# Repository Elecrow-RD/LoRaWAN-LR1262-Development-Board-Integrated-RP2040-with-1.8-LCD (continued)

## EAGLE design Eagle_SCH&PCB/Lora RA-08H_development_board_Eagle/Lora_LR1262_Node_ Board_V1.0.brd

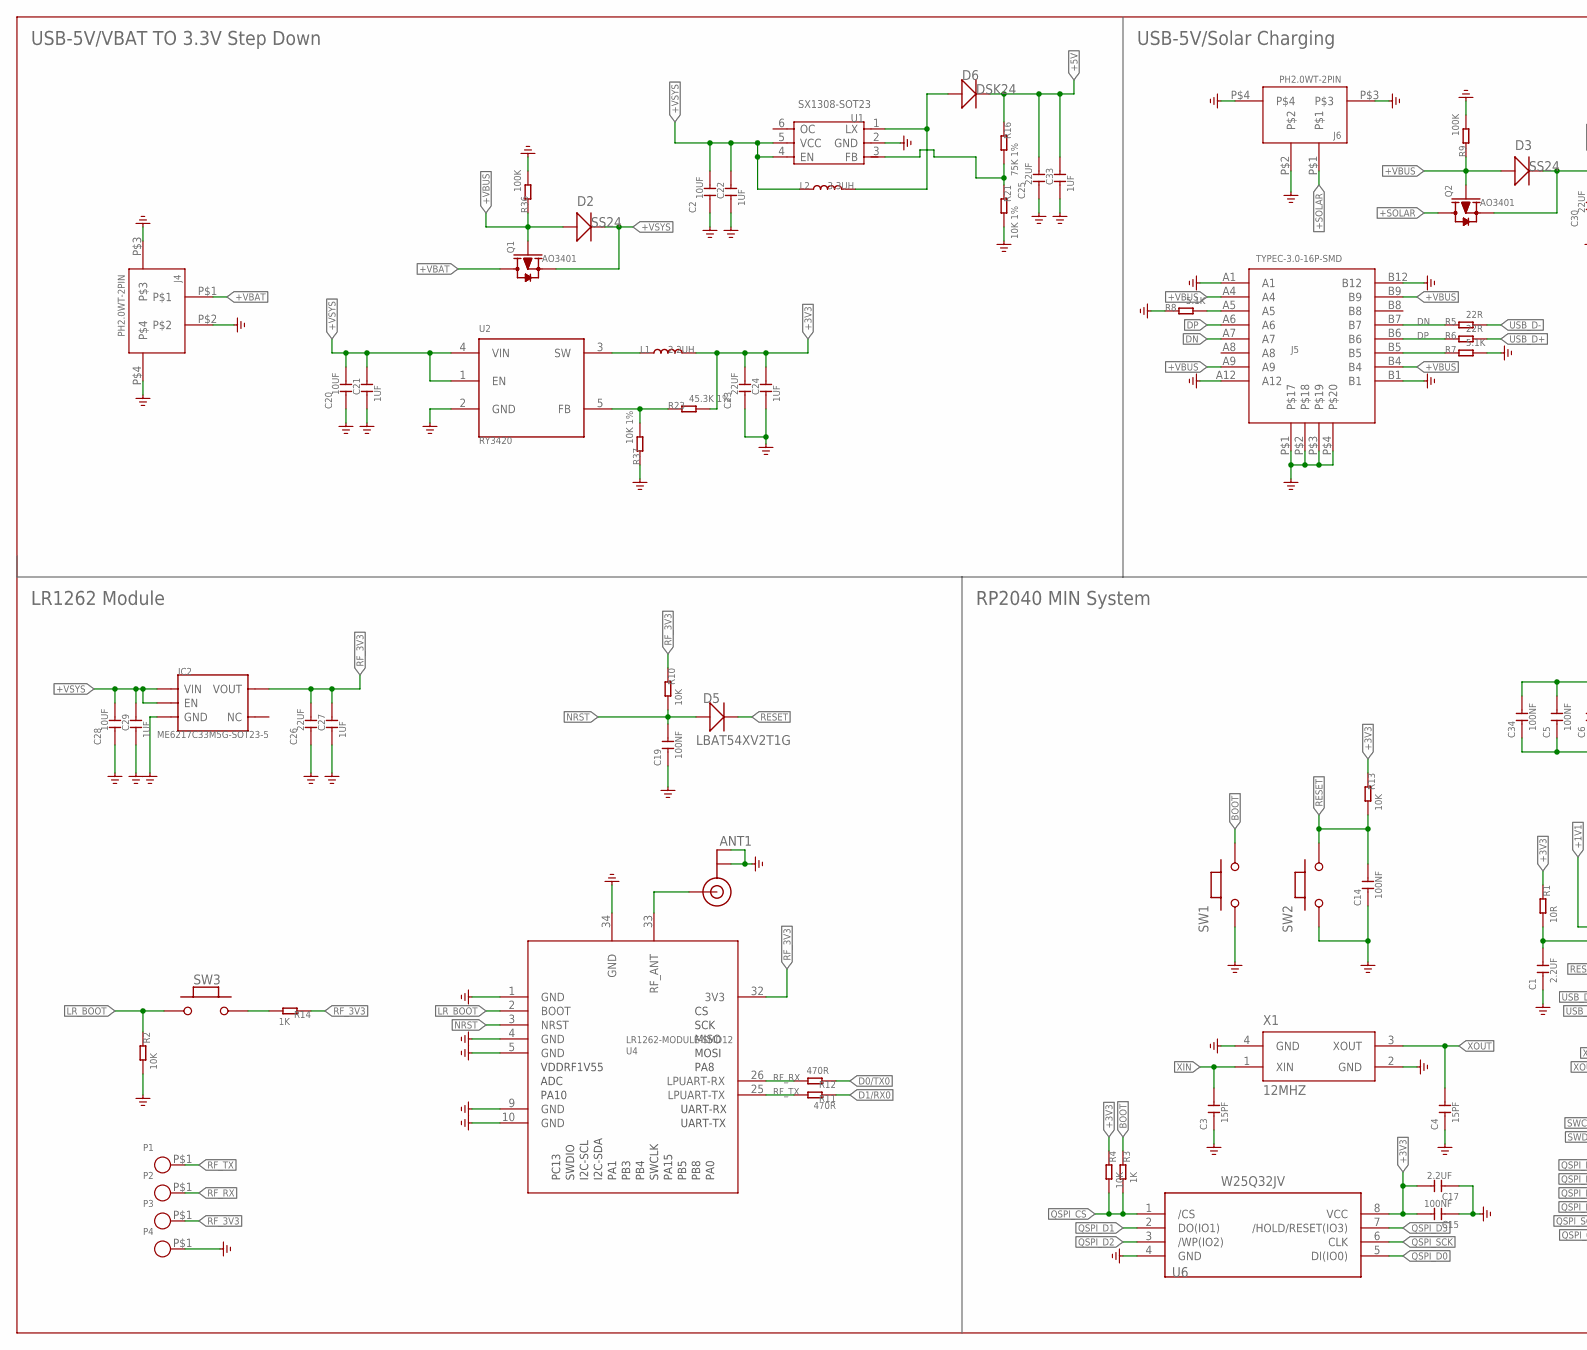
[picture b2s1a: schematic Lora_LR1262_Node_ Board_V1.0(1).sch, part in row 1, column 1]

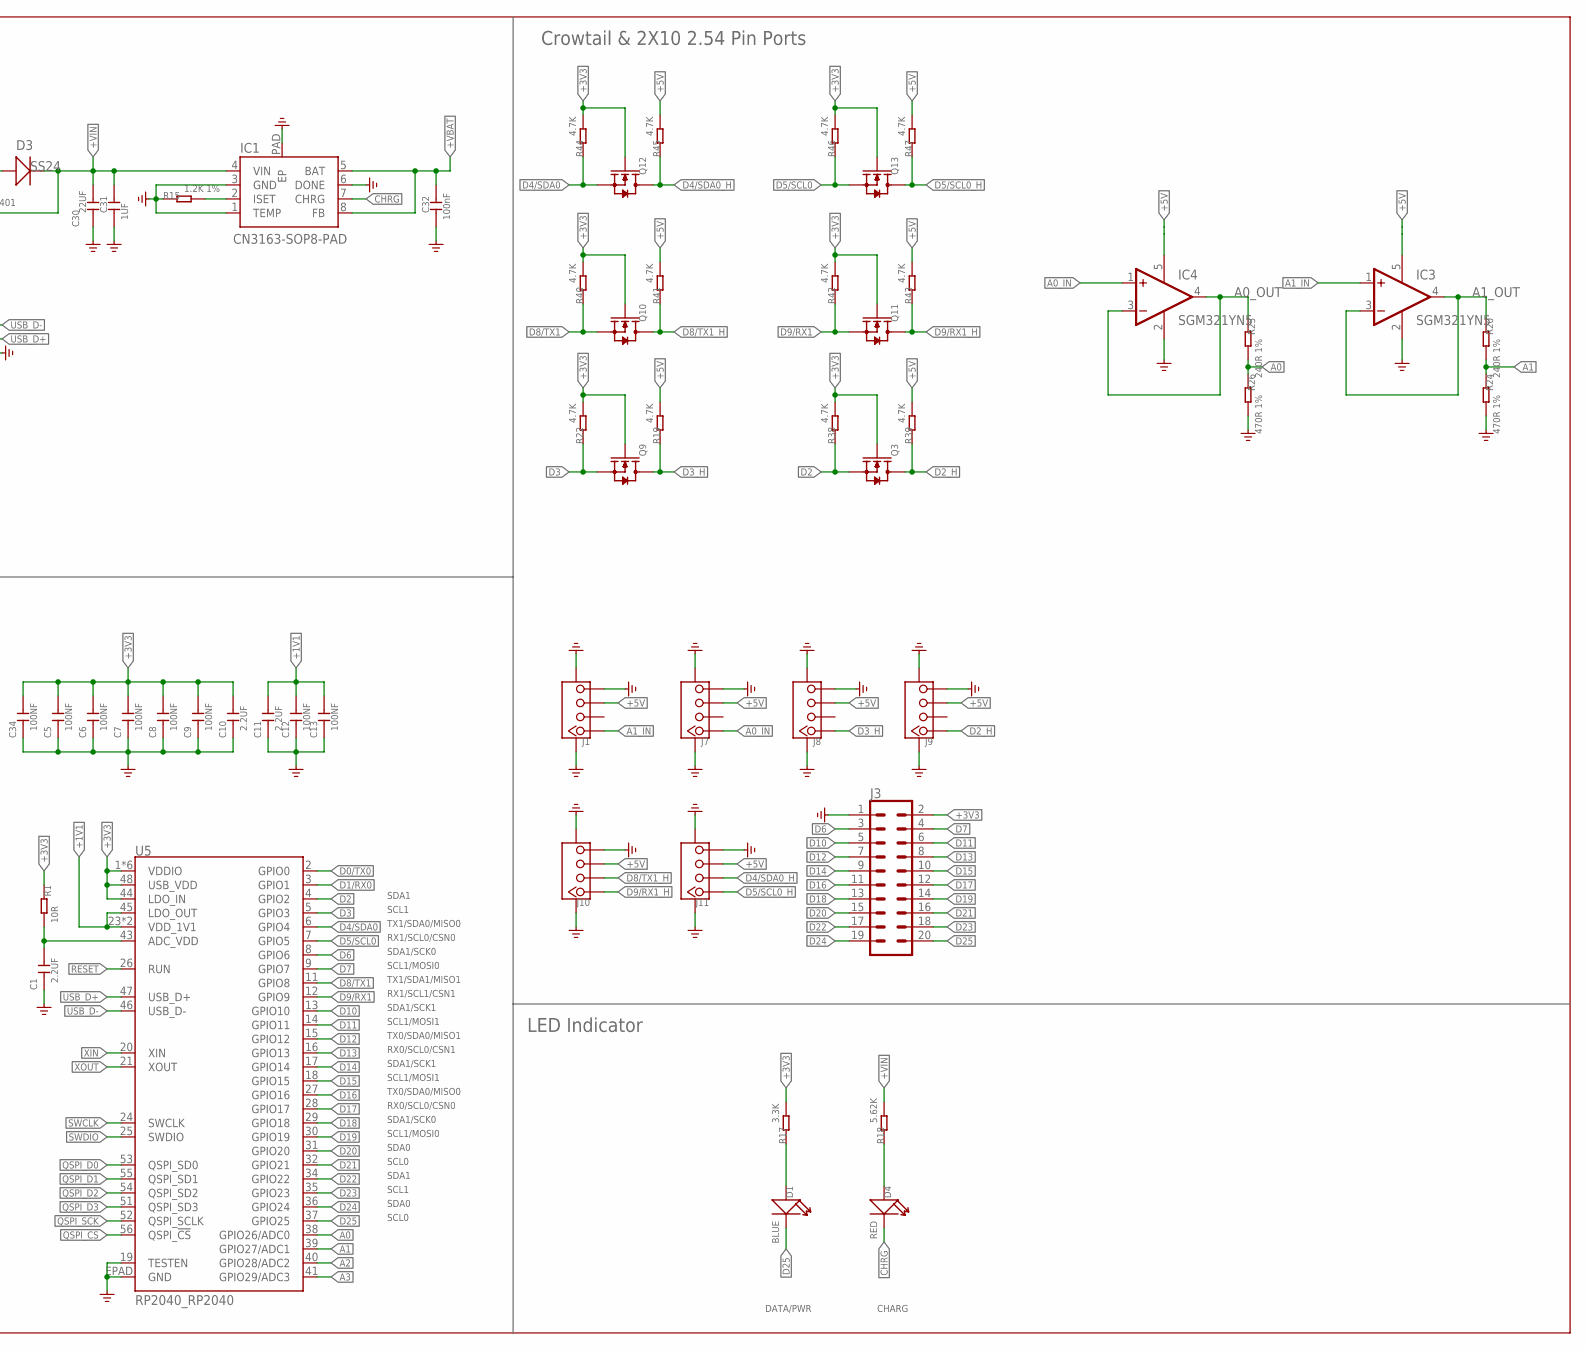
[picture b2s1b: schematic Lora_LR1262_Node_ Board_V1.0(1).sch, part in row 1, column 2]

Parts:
ANT1: SPARKFUN2_U.FL
C1, C10, C11, C17: 2.2UF; 0402
C2, C20, C28: 10UF; C0805
C3, C4: 15PF; 0402
C5, C6, C7, C8, C9, C12, C13, C14, C15, C19, C34: 100NF; 0402
C21, C22, C24, C27, C29, C31, C33: 1UF; C0603
C23, C25, C26, C30: 22UF; C0805
C32: 100nF; C0603
D1: BLUE; LED0603
D2, D3: SS24; SMA
D4: RED; LED0603
D5: LBAT54XV2T1G; D_SOD523
D6: DSK24; D_SOD123FL
IC1: CN3163-SOP8-PAD; SOP8-PAD
IC2: ME6217C33M5G-SOT23-5; IC_SOT23-5
IC3, IC4: SGM321YN5; SOT23-5
J1, J7, J8, J9, J10, J11: CONNECTOR_TWIG-4P-2.0-SMD-FEMALE-REINFORCE90D; CONNECTOR_4P-SMD-2.0-90D
J3: CONN_10X22X10-DSY-P2.54; 2X10-DSY-P2.54
J4, J6: PH2.0WT-2PIN
J5: TYPEC-3.0-16P-SMD; KEVIN_3.0TYPEC-SMD
L1: 2.2UH; L0420
L2: 3.3UH; L0420
P1, P2, P3, P4: TEST_PADPAD-1.5MM; TEST_PAD-1.5MM
Q1, Q2: AO3401; PMOS_SOT23
Q3, Q9, Q10, Q11, Q12, Q13: MOSFET-NSI1304BDL; MOS_SOT323
R1: 10R; R0402
R2, R4, R10, R13: 10K; R0402
R3, R14: 1K; R0402
R5, R6: 22R; R0402
R7, R8: 5.1K; R0402
R9, R36: 100K; R0402
R11, R12: 470R; R0402
R15: 1.2K 1%; R0402
R16: 75K 1%; R0402
R17: 3.3K; R0402
R18: 5.62K; R0402
R19, R22, R38, R39, R40, R41, R42, R43, R44, R45, R46, R47: 4.7K; R0402
R20, R25: 240R 1%; R0402
R21, R37: 10K 1%; R0402
R23: 45.3K 1%; R0402
R24, R26: 470R 1%; R0402
SW1, SW2, SW3: MYSMD_PB157_4.3X3; MYSMD_157SW
U1: SX1308-SOT23; STUDY_SOT23-6L
U2: RY3420; IC_SOT23-5
U4: LR1262-MODULE-SMD12
U5: RP2040_RP2040; RP2040_QFN-56
U6: W25Q32JV; SELF_SOIC-8-208MIL
X1: 12MHZ; SMD3225

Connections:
+1V1: C11.2, C12.2, C13.2, U5.23 (VDD_1V1), U5.45 (LDO_OUT), U5.50 (VDD_1V1)
+3V3: C5.2, C6.2, C7.2, C8.2, C9.2, C10.2, C15.2, C17.2, C23.2, C24.2, C34.2, J3.2, L1.2, Q3.1 (G), Q9.1 (G), Q10.1 (G), Q11.1 (G), Q12.1 (G), Q13.1 (G), R1.1, R4.1, R13.1, R17.2, R22.2, R23.2, R38.2, R40.2, R42.2, R44.2, R46.2, U5.1 (VDDIO), U5.10 (VDDIO), U5.22 (VDDIO), U5.33 (VDDIO), U5.42 (VDDIO), U5.44 (LDO_IN), U5.48 (USB_VDD), U5.49 (VDDIO), U6.8 (VCC)
+5V: C25.2, C33.2, D6.-, IC3.5 (V+), IC4.5 (V+), J1.3, J7.3, J8.3, J9.3, J10.3, J11.3, R16.1, R19.2, R39.2, R41.2, R43.2, R45.2, R47.2
+SOLAR: J6.P$1, Q2.3 (D)
+VBAT: C32.2, IC1.5 (BAT), IC1.8 (FB), J4.P$1, Q1.3 (D)
+VBUS: D2.2 (+), D3.2 (+), J5.A4, J5.A9, J5.B4, J5.B9, Q1.1 (G), Q2.1 (G), R9.1, R36.1
+VIN: C30.2, C31.2, D3.1 (-), IC1.4 (VIN), Q2.2 (S), R18.2
+VSYS: C2.2, C20.2, C21.2, C22.2, C28.2, C29.2, D2.1 (-), IC2.1 (VIN), IC2.3 (EN), L2.1, Q1.2 (S), U1.4 (EN), U1.5 (VCC), U2.1 (EN), U2.4 (VIN)
A0: R25.2, R26.1, U5.38 (GPIO26/ADC0)
A0_IN: IC4.1 (+IN), J7.1
A0_OUT: IC4.3 (-IN), IC4.4 (OUT), R25.1
A1: R20.2, R24.1, U5.39 (GPIO27/ADC1)
A1_IN: IC3.1 (+IN), J1.1
A1_OUT: IC3.3 (-IN), IC3.4 (OUT), R20.1
A2: U5.40 (GPIO28/ADC2)
A3: U5.41 (GPIO29/ADC3)
BOOT: R3.1, SW1.2
CHRG: D4.-, IC1.7 (CHRG)
D0/TX0: R12.1, U5.2 (GPIO0)
D1/RX0: R11.1, U5.3 (GPIO1)
D2: Q3.2 (S), R38.1, U5.4 (GPIO2)
D2_H: J9.1, Q3.3 (D), R39.1
D3: Q9.2 (S), R22.1, U5.5 (GPIO3)
D3_H: J8.1, Q9.3 (D), R19.1
D4/SDA0: Q12.2 (S), R44.1, U5.6 (GPIO4)
D4/SDA0_H: J11.2, Q12.3 (D), R45.1
D5/SCL0: Q13.2 (S), R46.1, U5.7 (GPIO5)
D5/SCL0_H: J11.1, Q13.3 (D), R47.1
D6: J3.3, U5.8 (GPIO6)
D7: J3.4, U5.9 (GPIO7)
D8/TX1: Q10.2 (S), R40.1, U5.11 (GPIO8)
D8/TX1_H: J10.2, Q10.3 (D), R41.1
D9/RX1: Q11.2 (S), R42.1, U5.12 (GPIO9)
D9/RX1_H: J10.1, Q11.3 (D), R43.1
D10: J3.5, U5.13 (GPIO10)
D11: J3.6, U5.14 (GPIO11)
D12: J3.7, U5.15 (GPIO12)
D13: J3.8, U5.16 (GPIO13)
D14: J3.9, U5.17 (GPIO14)
D15: J3.10, U5.18 (GPIO15)
D16: J3.11, U5.27 (GPIO16)
D17: J3.12, U5.28 (GPIO17)
D18: J3.13, U5.29 (GPIO18)
D19: J3.14, U5.30 (GPIO19)
D20: J3.15, U5.31 (GPIO20)
D21: J3.16, U5.32 (GPIO21)
D22: J3.17, U5.34 (GPIO22)
D23: J3.18, U5.35 (GPIO23)
D24: J3.19, U5.36 (GPIO24)
D25: D1.-, J3.20, U5.37 (GPIO25)
DN: J5.A7, J5.B7, R5.1
DP: J5.A6, J5.B6, R6.1
GND: ANT1.P$1 (GND), ANT1.P$2 (GND), C1.1, C2.1, C3.1, C4.1, C5.1, C6.1, C7.1, C8.1, C9.1, C10.1, C11.1, C12.1, C13.1, C14.1, C15.1, C17.1, C19.1, C20.1, C21.1, C22.1, C23.1, C24.1, C25.1, C26.1, C27.1, C28.1, C29.1, C30.1, C31.1, C32.1, C33.1, C34.1, IC1.1 (TEMP), IC1.3 (GND), IC1.6 (DONE), IC1.PAD (EP), IC2.2 (GND), IC3.2 (V-), IC4.2 (V-), J1.4, J1.SS1, J1.SS2, J3.1, J4.P$2, J4.P$3, J4.P$4, J5.A1, J5.A12, J5.B1, J5.B12, J5.P$1, J5.P$2, J5.P$3, J5.P$4, J6.P$2, J6.P$3, J6.P$4, J7.4, J7.SS1, J7.SS2, J8.4, J8.SS1, J8.SS2, J9.4, J9.SS1, J9.SS2, J10.4, J10.SS1, J10.SS2, J11.4, J11.SS1, J11.SS2, P4.P$1, R2.2, R7.2, R8.1, R9.2, R15.1, R21.2, R24.2, R26.2, R36.2, R37.1, SW1.1, SW2.1, U1.2 (GND), U2.2 (GND), U4.1 (GND), U4.4 (GND), U4.5 (GND), U4.9 (GND), U4.10 (GND), U4.34 (GND), U5.19 (TESTEN), U5.EPAD (GND), U6.4 (GND), X1.2 (GND), X1.4 (GND)
LR_BOOT: R2.1, SW3.1, U4.2 (BOOT)
unnamed: C1.2, R1.2, U5.43 (ADC_VDD)
unnamed: J5.B5, R7.1
unnamed: L1.1, U2.3 (SW)
unnamed: D6.+, L2.2, U1.1 (LX)
unnamed: J5.A5, R8.2
unnamed: R14.2, SW3.2
unnamed: ANT1.P$3 (SIGNAL), U4.33 (RF_ANT)
unnamed: R23.1, R37.2, U2.5 (FB)
unnamed: IC1.2 (ISET), R15.2
unnamed: D4.+, R18.1
unnamed: R16.2, R21.1, U1.3 (FB)
unnamed: D1.+, R17.1
NRST: C19.2, D5.+, R10.2, U4.3 (NRST)
QSPI_CS: R3.2, R4.2, U5.56 (QSPI_!CS!), U6.1 (/CS)
QSPI_D0: U5.53 (QSPI_SD0), U6.5 (DI(IO0))
QSPI_D1: U5.55 (QSPI_SD1), U6.2 (DO(IO1))
QSPI_D2: U5.54 (QSPI_SD2), U6.3 (/WP(IO2))
QSPI_D3: U5.51 (QSPI_SD3), U6.7 (/HOLD/RESET(IO3))
QSPI_SCK: U5.52 (QSPI_SCLK), U6.6 (CLK)
RESET: C14.2, D5.-, R13.2, SW2.2, U5.26 (RUN)
RF_3V3: C26.2, C27.2, IC2.5 (VOUT), P3.P$1, R10.1, R14.1, U4.32 (3V3)
RF_RX: P2.P$1, R12.2, U4.26 (LPUART-RX)
RF_TX: P1.P$1, R11.2, U4.25 (LPUART-TX)
SWCLK: U5.24 (SWCLK)
SWDIO: U5.25 (SWDIO)
USB_D+: R6.2, U5.47 (USB_D+)
USB_D-: R5.2, U5.46 (USB_D-)
XIN: C3.2, U5.20 (XIN), X1.1 (XIN)
XOUT: C4.2, U5.21 (XOUT), X1.3 (XOUT)

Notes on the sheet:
USB-5V/VBAT TO 3.3V Step Down
USB-5V/Solar Charging
LR1262 Module
RP2040 MIN System
Crowtail & 2X10 2.54 Pin Ports
LED Indicator
DATA/PWR
CHARG
SDA1
SCL1
TX1/SDA0/MISO0
RX1/SCL0/CSN0
SDA1/SCK0
SCL1/MOSI0
TX1/SDA1/MISO1
RX1/SCL1/CSN1
SDA1/SCK1
SCL1/MOSI1
TX0/SDA0/MISO1
RX0/SCL0/CSN1
TX0/SDA0/MISO0
RX0/SCL0/CSN0
SDA0
SCL0

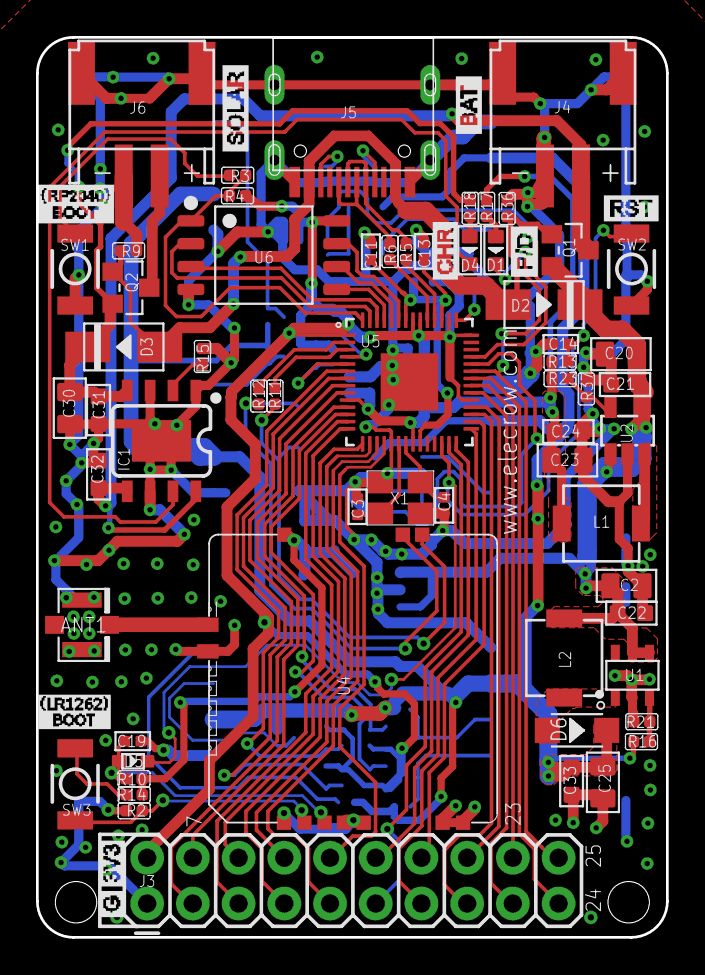
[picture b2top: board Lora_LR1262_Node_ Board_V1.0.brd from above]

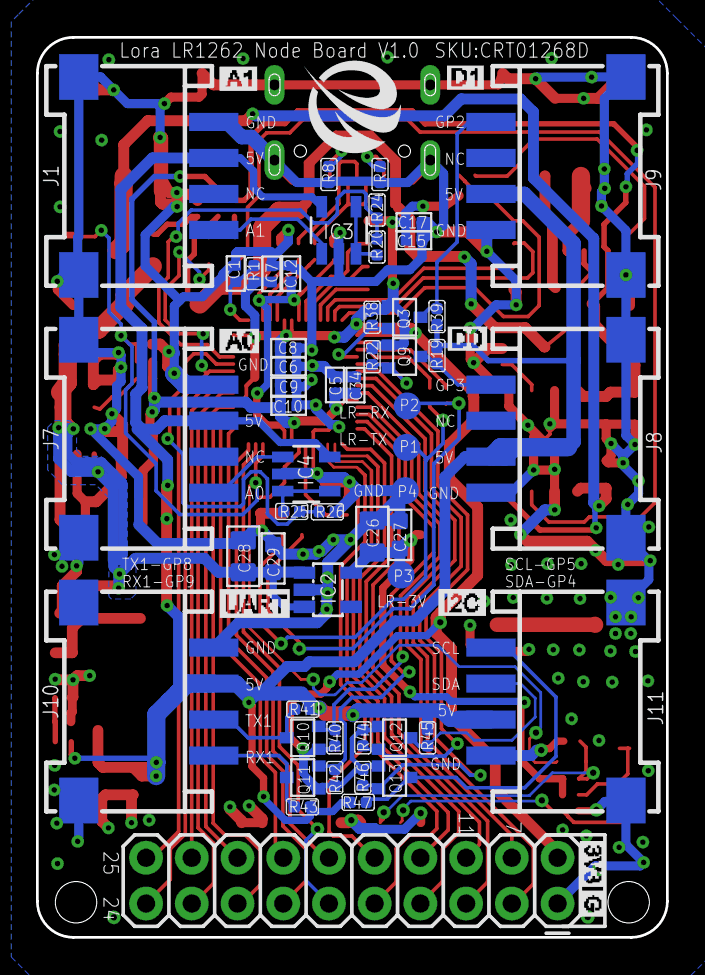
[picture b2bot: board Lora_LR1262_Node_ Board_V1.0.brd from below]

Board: 2 copper layers, 35.0 x 50.0 mm, 115 parts (54 on the bottom side), 79 nets.

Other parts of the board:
U$55: ELECROW-NEW
